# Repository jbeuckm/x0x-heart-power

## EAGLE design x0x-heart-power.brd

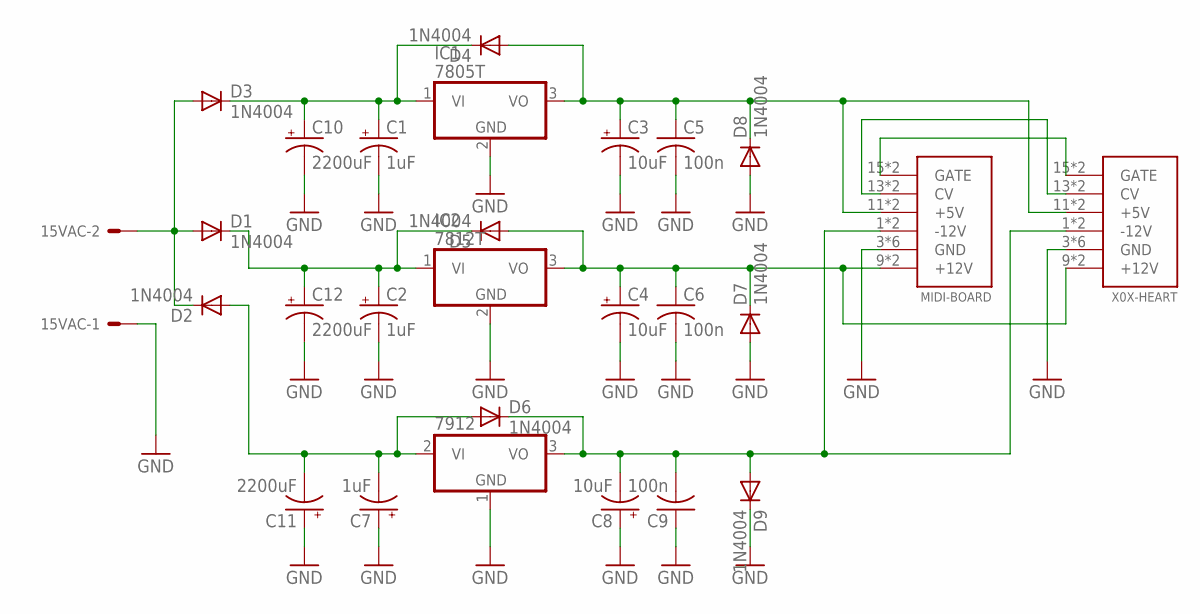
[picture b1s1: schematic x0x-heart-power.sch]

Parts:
15VAC: KK-156-2
7912: 7912T; TO220H
C1, C2, C7: 1uF; E2-5
C3, C4, C8: 10uF; E2-5
C5, C6, C9: 100n; C025-024X044
C10, C11, C12: 2200uF; E22-6
D1, D2, D3, D4, D5, D6, D7, D8, D9: 1N4004; DO41-10
IC1: 7805T; TO220H
IC2: 7812T; TO220H
MIDI-BOARD: POWER; POWER_16
X0X-HEART: POWER; POWER_16

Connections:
GND: 15VAC.1, 7912.1 (GND), C1.-, C2.-, C3.-, C4.-, C5.2, C6.2, C7.+, C8.+, C9.1, C10.-, C11.+, C12.-, D7.A, D8.A, D9.C, IC1.2 (GND), IC2.2 (GND), MIDI-BOARD.3 (GND), MIDI-BOARD.4 (GND), MIDI-BOARD.5 (GND), MIDI-BOARD.6 (GND), MIDI-BOARD.7 (GND), MIDI-BOARD.8 (GND), X0X-HEART.3 (GND), X0X-HEART.4 (GND), X0X-HEART.5 (GND), X0X-HEART.6 (GND), X0X-HEART.7 (GND), X0X-HEART.8 (GND)
unnamed: MIDI-BOARD.15 (GATE), MIDI-BOARD.16 (GATE), X0X-HEART.15 (GATE), X0X-HEART.16 (GATE)
unnamed: MIDI-BOARD.13 (CV), MIDI-BOARD.14 (CV), X0X-HEART.13 (CV), X0X-HEART.14 (CV)
unnamed: C3.+, C5.1, D4.A, D8.C, IC1.3 (VO), MIDI-BOARD.11 (+5V), MIDI-BOARD.12 (+5V), X0X-HEART.11 (+5V), X0X-HEART.12 (+5V)
unnamed: 7912.2 (VI), C7.-, C11.-, D2.A, D6.A
unnamed: 7912.3 (VO), C8.-, C9.2, D6.C, D9.A, MIDI-BOARD.1 (-12V), MIDI-BOARD.2 (-12V), X0X-HEART.1 (-12V), X0X-HEART.2 (-12V)
unnamed: C1.+, C10.+, D3.C, D4.C, IC1.1 (VI)
unnamed: C4.+, C6.1, D5.A, D7.C, IC2.3 (VO), MIDI-BOARD.9 (+12V), MIDI-BOARD.10 (+12V), X0X-HEART.9 (+12V), X0X-HEART.10 (+12V)
unnamed: C2.+, C12.+, D1.C, D5.C, IC2.1 (VI)
unnamed: 15VAC.2, D1.A, D2.C, D3.A

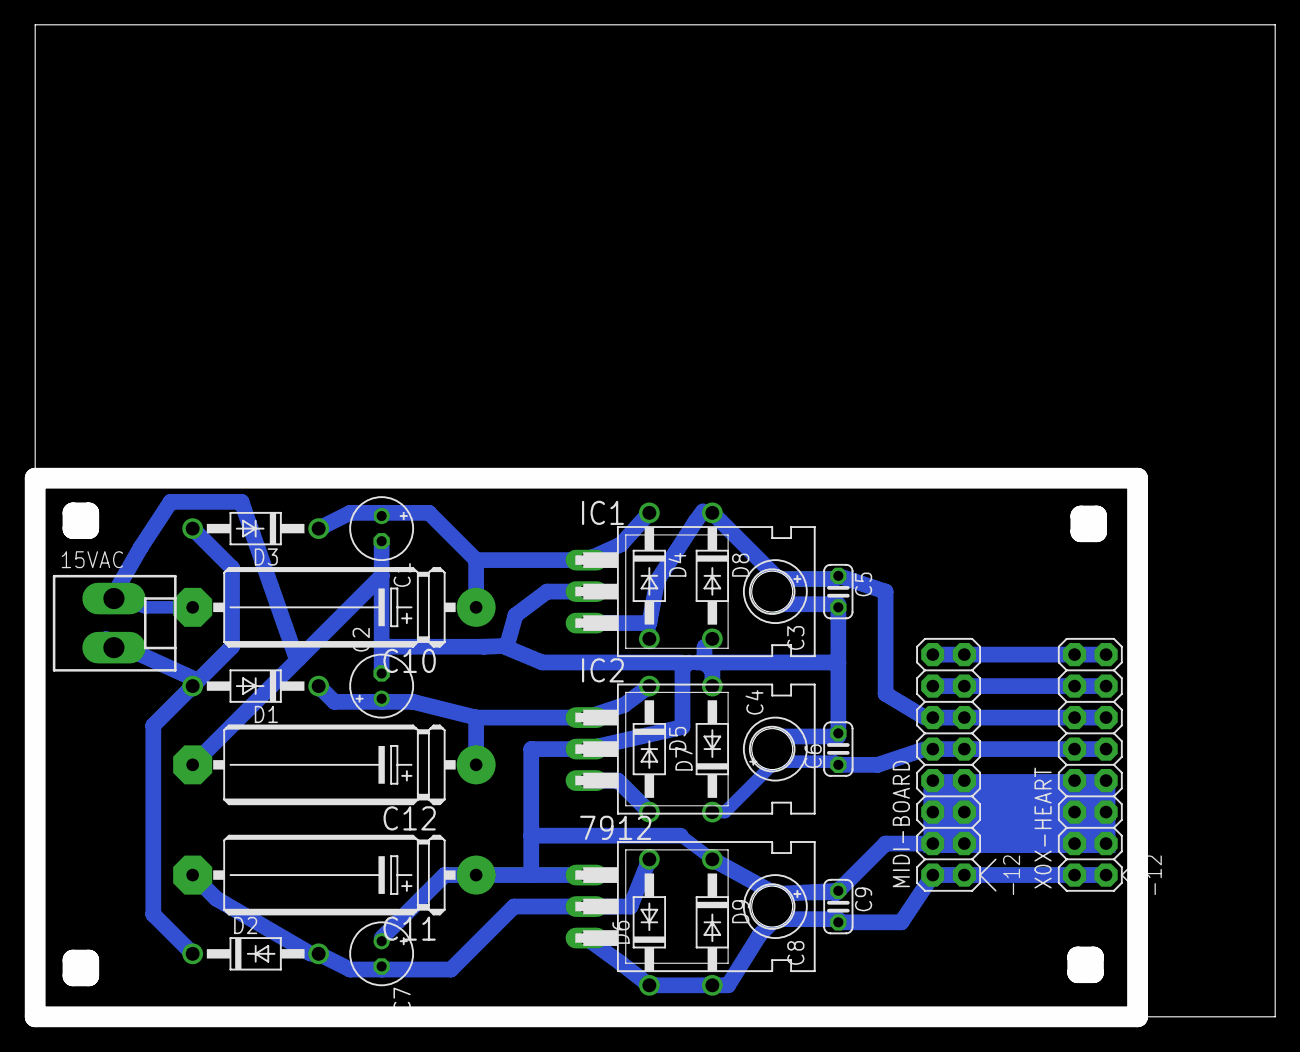
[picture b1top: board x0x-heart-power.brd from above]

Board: 2 copper layers, 99.2 x 79.2 mm, 27 parts (0 on the bottom side), 10 nets.

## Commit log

2016-03-18 added negative 12
2016-03-19 tweaks
2016-03-19 gcode
2016-03-31 fixed missing trace
